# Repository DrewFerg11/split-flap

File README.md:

# split-flap
3D-printable split-flap modules, electronics, and firmware

[Documentation and demos](https://drewferg11.github.io/split-flap/) (site under development).

## Layout

| Folder | What | Release tag |
|---|---|---|
| [`pcb/`](pcb/) | KiCad boards; fab packages built locally and committed | `pcb/<board>/vX.Y` |
| [`hardware/`](hardware/) | 3D-printable and physical parts | `hw/<part>/vX.Y` |
| [`firmware/`](firmware/) | Shared module and controller firmware; built by CI | `fw/<target>/vX.Y.Z` |
| [`applications/`](applications/) | Displays built from the above (e.g. Premier League) | `app/<application>/vX.Y.Z` |

## License

Free to build, modify, and share for noncommercial use under
[CC BY-NC-SA 4.0](LICENSE.md), with a few extra permissions (paying a fab for your own
build, selling a used personal build, platform rewards on remixes). Commercial use needs
permission. See [LICENSE.md](LICENSE.md), [THIRD-PARTY-NOTICES.md](LICENSES/THIRD-PARTY-NOTICES.md),
and [CONTRIBUTING.md](.github/CONTRIBUTING.md).

This is original work; see the [Acknowledgements](LICENSE.md#acknowledgements) for the projects
we're grateful to.

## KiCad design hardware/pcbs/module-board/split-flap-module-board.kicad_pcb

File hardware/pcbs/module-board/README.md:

# Split-flap module board v0.1

**Status (2026-10-27): board #1 brought up** (power, SWD flash, LED, hall, encoder, motor drive all pass; see `design/DESIGN-1.md` section 14 and `firmware/ltm-bringup/`). **Next:** other 9 boards, ISEN, RS-485 + enumeration firmware.

**Status (2026-10-19): ordered.** ERC 0, DRC 0 errors / 0 unconnected; the files in `fab/` are what was ordered.

**Ordered 2026-10-19:** JLCPCB, 10 boards, Economic PCBA top side (green, 1.6 mm, HASL), est. ship 2026-10-23; C1 hand-solder caps from LCSC (20× C3151830, separate shipment).

Start with [`design/DESIGN-1.md`](design/DESIGN-1.md).

One small board per split-flap module (digit and name) of the league-table display
([`builds/league-table`](../../builds/league-table/README.md)): STM32G031 + DRV8870 driving one 12 V
N20 encoder motor, A3144 homing, RS-485 to a single ESP32 host, chained module-to-module through
right-angle headers on the board edges.

The hall sensor connector and pinout are the same as on the SplitFlap v5.1 board, so existing
sensor leads plug in.

```
design/
  DESIGN-1.md          requirements, decisions, parts, pin map, outline, open questions  <- read this
(project root)
  split-flap-module-board.kicad_pro/_sch    KiCad 10 project (generated by scripts/)
  split-flap-module-board-schematic.pdf
  split-flap-module-board.kicad_pcb         32 x 54 mm, 2 layers (generated by scripts/)
  split-flap-module-board.kicad_sym  project symbols (library sfmb:) (+12V_CHAIN/FUSED/LOCAL, GM3085E)
  fab/                 JLC package: gerbers/ + zip, BOM, CPL, STEP, layers PDF, check reports
    images/            top / bottom / 3D renders and screenshots
  scripts/             build.py: schematic + ERC + PDF + netlist
                       route_all.py: placement -> GND fan-out -> Freerouting -> stitch/fill -> silk ->
                       width audit -> DRC -> fab outputs (gen_board, stitch, autoroute, silk, widths,
                       outputs, jlc_cpl, snap, check_place)
```

```
python scripts/build.py        # schematic (seconds)
python scripts/route_all.py    # board + fab package (~10 min, Freerouting)
```

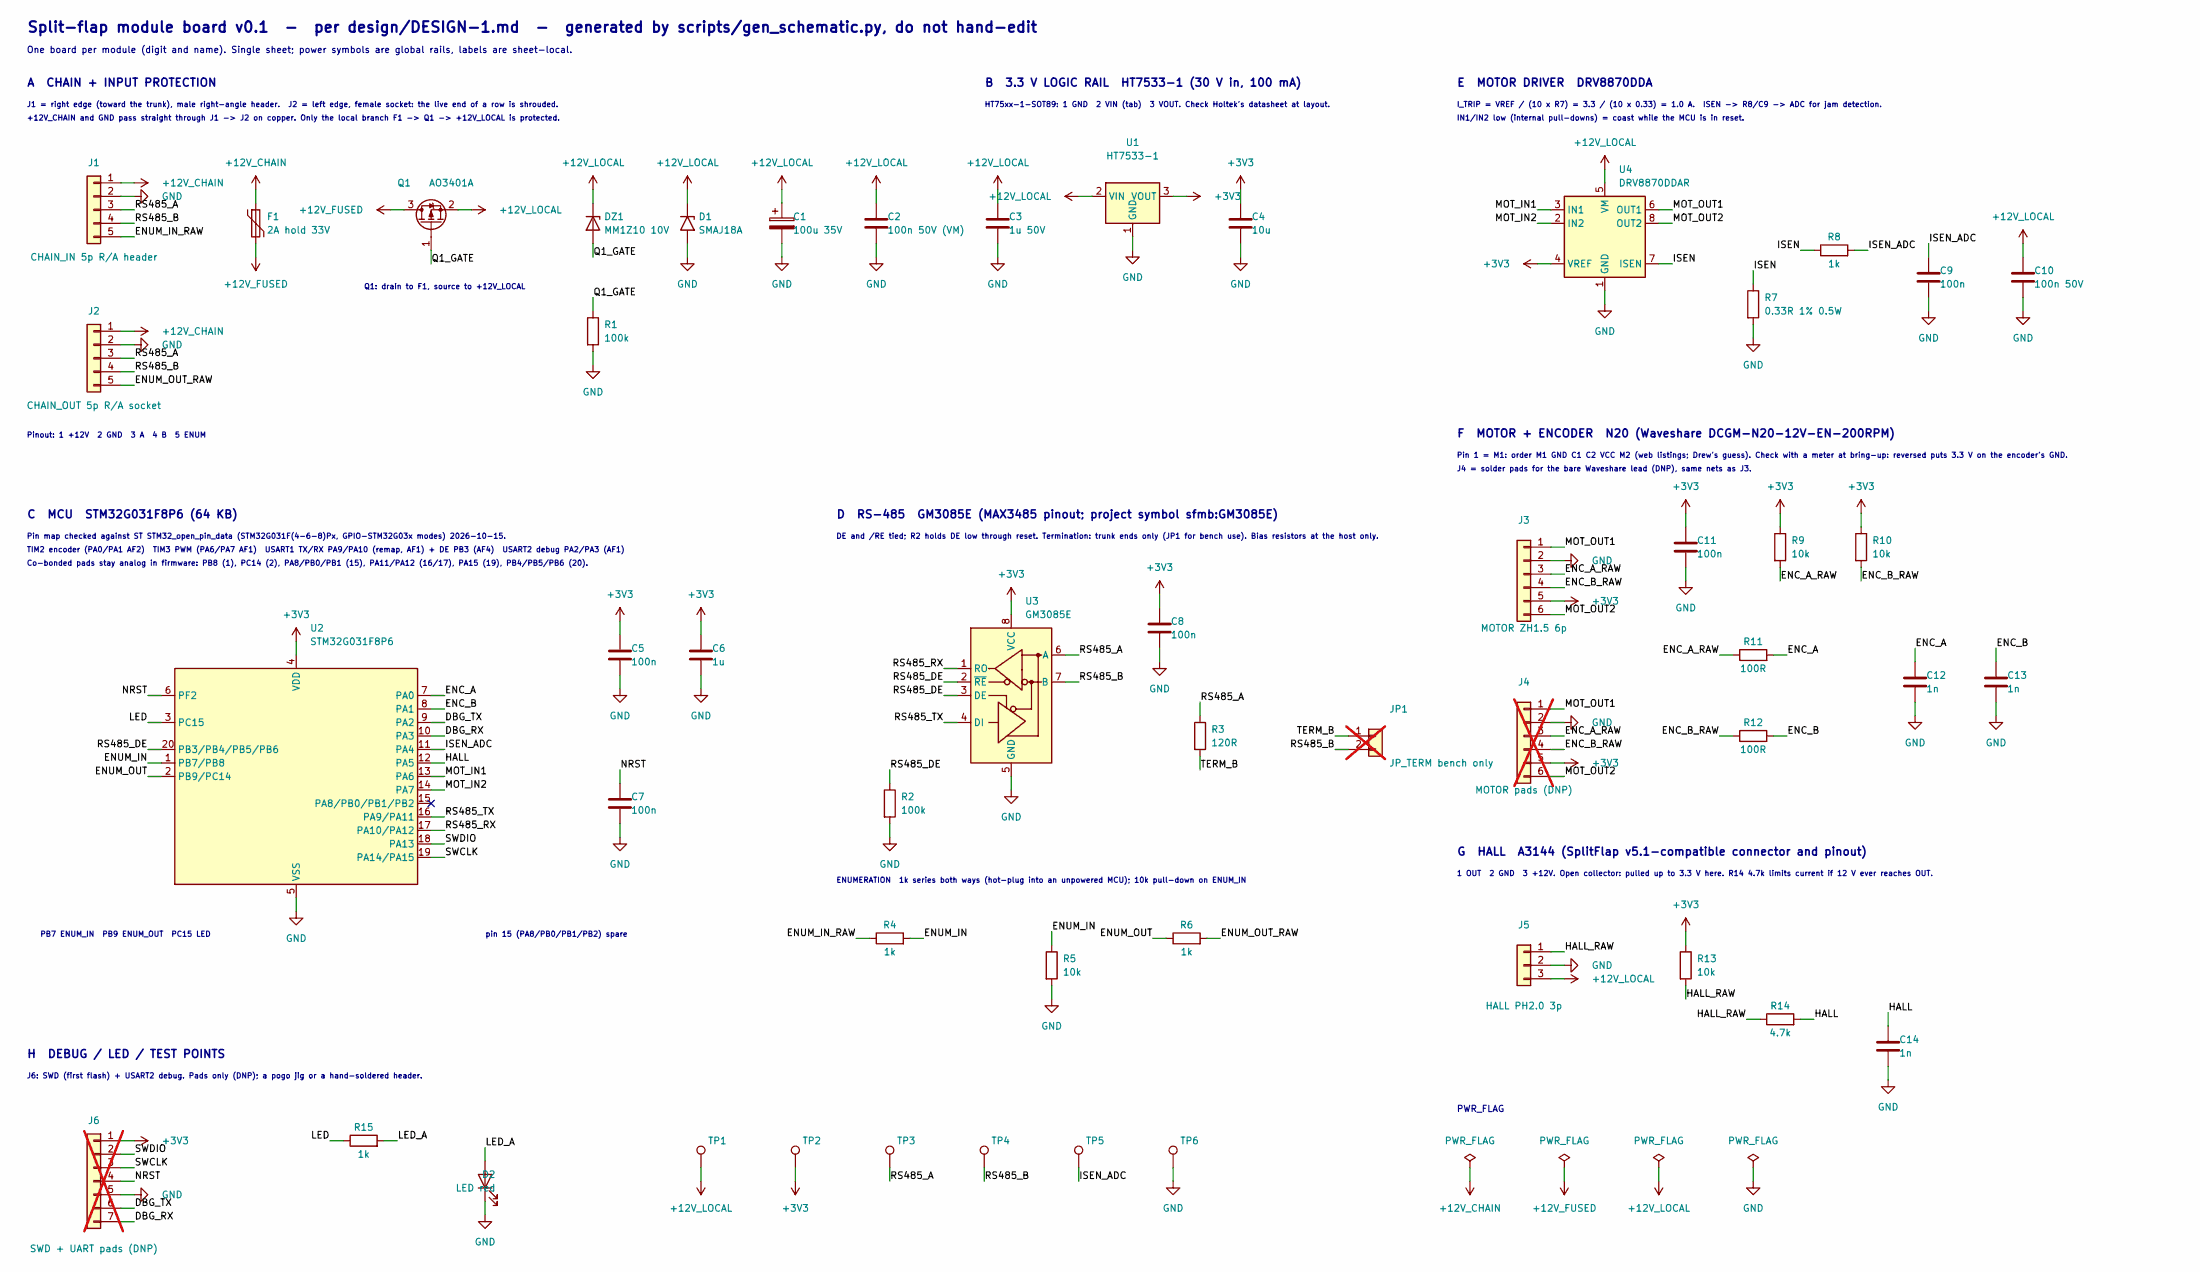
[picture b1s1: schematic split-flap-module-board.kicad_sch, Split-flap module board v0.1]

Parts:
C1: 100u 35V; CP_Elec_6.3x5.4; LCSC C3151830
C2: 100n 50V (VM); C_0603_1608Metric; LCSC C14663
C3: 1u 50V; C_0603_1608Metric; LCSC C15849
C4: 10u; C_0603_1608Metric; LCSC C19702
C5, C7, C8, C9, C11: 100n; C_0603_1608Metric; LCSC C14663
C6: 1u; C_0603_1608Metric; LCSC C15849
C10: 100n 50V; C_0603_1608Metric; LCSC C14663
C12, C13, C14: 1n; C_0603_1608Metric; LCSC C1588
D1: SMAJ18A; D_SMA; LCSC C908771
D2: LED red; LED_0603_1608Metric; LCSC C2286
DZ1: MM1Z10 10V; D_SOD-123; LCSC C107591
F1: 2A hold 33V; Fuse_1812_4532Metric; LCSC C7433877
J1: CHAIN_IN 5p R/A header; PinHeader_1x05_P2.54mm_Horizontal; LCSC C492413
J2: CHAIN_OUT 5p R/A socket; PinSocket_1x05_P2.54mm_Horizontal; LCSC C2897387
J3: MOTOR ZH1.5 6p; JST_ZH_B6B-ZR_1x06_P1.50mm_Vertical; LCSC C157984
J4: MOTOR pads (DNP); PinHeader_1x06_P2.54mm_Vertical; not fitted
J5: HALL PH2.0 3p; JST_PH_B3B-PH-K_1x03_P2.00mm_Vertical; LCSC C2320
J6: SWD + UART pads (DNP); PinHeader_1x07_P2.54mm_Vertical; not fitted
JP1: JP_TERM bench only; PinHeader_1x02_P2.54mm_Vertical; LCSC C492401; not fitted
Q1: AO3401A; SOT-23; LCSC C15127
R1, R2: 100k; R_0603_1608Metric; LCSC C25803
R3: 120R; R_0603_1608Metric; LCSC C22787
R4, R6, R8, R15: 1k; R_0603_1608Metric; LCSC C21190
R5, R9, R10, R13: 10k; R_0603_1608Metric; LCSC C25804
R7: 0.33R 1% 0.5W; R_1206_3216Metric; LCSC C858786
R11, R12: 100R; R_0603_1608Metric; LCSC C22775
R14: 4.7k; R_0603_1608Metric; LCSC C23162
TP1: +12V_LOCAL; TestPoint_Pad_D1.5mm
TP2: +3V3; TestPoint_Pad_D1.5mm
TP3: RS485_A; TestPoint_Pad_D1.5mm
TP4: RS485_B; TestPoint_Pad_D1.5mm
TP5: ISEN_ADC; TestPoint_Pad_D1.5mm
TP6: GND; TestPoint_Pad_D1.5mm
U1: HT7533-1; SOT-89-3; LCSC C14289
U2: STM32G031F8P6; TSSOP-20_4.4x6.5mm_P0.65mm; LCSC C529334
U3: GM3085E; SOIC-8_3.9x4.9mm_P1.27mm; LCSC C269864
U4: DRV8870DDAR; Texas_HTSOP-8-1EP_3.9x4.9mm_P1.27mm_EP2.95x4.9mm_Mask2.4x3.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; LCSC C86590

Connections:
+3V3: C4.1, C5.1, C6.1, C8.1, C11.1, J3.5, J4.5, J6.1, R9.1, R10.1, R13.1, TP2.1, U1.3 (VOUT), U2.4 (VDD), U3.8 (VCC), U4.4 (VREF)
+12V_CHAIN: F1.1, J1.1, J2.1
+12V_FUSED: F1.2, Q1.3 (D)
+12V_LOCAL: C1.1, C2.1, C3.1, C10.1, D1.1 (A1), DZ1.1 (K), J5.3, Q1.2 (S), TP1.1, U1.2 (VIN), U4.5 (VM)
/DBG_RX: J6.7, U2.10 (PA3)
/DBG_TX: J6.6, U2.9 (PA2)
/ENC_A: C12.1, R11.2, U2.7 (PA0)
/ENC_A_RAW: J3.3, J4.3, R9.2, R11.1
/ENC_B: C13.1, R12.2, U2.8 (PA1)
/ENC_B_RAW: J3.4, J4.4, R10.2, R12.1
/ENUM_IN: R4.2, R5.1, U2.1 (PB7/PB8)
/ENUM_IN_RAW: J1.5, R4.1
/ENUM_OUT: R6.1, U2.2 (PB9/PC14)
/ENUM_OUT_RAW: J2.5, R6.2
/HALL: C14.1, R14.2, U2.12 (PA5)
/HALL_RAW: J5.1, R13.2, R14.1
/ISEN: R7.1, R8.1, U4.7 (ISEN)
/ISEN_ADC: C9.1, R8.2, TP5.1, U2.11 (PA4)
/LED: R15.1, U2.3 (PC15)
/LED_A: D2.2 (A), R15.2
/MOT_IN1: U2.13 (PA6), U4.3 (IN1)
/MOT_IN2: U2.14 (PA7), U4.2 (IN2)
/MOT_OUT1: J3.1, J4.1, U4.6 (OUT1)
/MOT_OUT2: J3.6, J4.6, U4.8 (OUT2)
/NRST: C7.1, J6.4, U2.6 (PF2)
/Q1_GATE: DZ1.2 (A), Q1.1 (G), R1.1
/RS485_A: J1.3, J2.3, R3.1, TP3.1, U3.6 (A)
/RS485_B: J1.4, J2.4, JP1.2, TP4.1, U3.7 (B)
/RS485_DE: R2.1, U2.20 (PB3/PB4/PB5/PB6), U3.2 (~RE), U3.3 (DE)
/RS485_RX: U2.17 (PA10/PA12), U3.1 (RO)
/RS485_TX: U2.16 (PA9/PA11), U3.4 (DI)
/SWCLK: J6.3, U2.19 (PA14/PA15)
/SWDIO: J6.2, U2.18 (PA13)
/TERM_B: JP1.1, R3.2
GND: C1.2, C2.2, C3.2, C4.2, C5.2, C6.2, C7.2, C8.2, C9.2, C10.2, C11.2, C12.2, C13.2, C14.2, D1.2 (A2), D2.1 (K), J1.2, J2.2, J3.2, J4.2, J5.2, J6.5, R1.2, R2.2, R5.2, R7.2, TP6.1, U1.1 (GND), U2.5 (VSS), U3.5 (GND), U4.1 (GND), U4.9 (GND)

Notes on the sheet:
A CHAIN + INPUT PROTECTION
J1 = right edge (toward the trunk), male right-angle header. J2 = left edge, female socket: the live end of a row is shrouded.
+12V_CHAIN and GND pass straight through J1 -> J2 on copper. Only the local branch F1 -> Q1 -> +12V_LOCAL is protected.
Pinout: 1 +12V 2 GND 3 A 4 B 5 ENUM
Q1: drain to F1, source to +12V_LOCAL
B 3.3 V LOGIC RAIL HT7533-1 (30 V in, 100 mA)
HT75xx-1-SOT89: 1 GND 2 VIN (tab) 3 VOUT. Check Holtek's datasheet at layout.
C MCU STM32G031F8P6 (64 KB)
Pin map checked against ST STM32_open_pin_data (STM32G031F(4-6-8)Px, GPIO-STM32G03x modes) 2026-10-15.
TIM2 encoder (PA0/PA1 AF2) TIM3 PWM (PA6/PA7 AF1) USART1 TX/RX PA9/PA10 (remap, AF1) + DE PB3 (AF4) USART2 debug PA2/PA3 (AF1)
Co-bonded pads stay analog in firmware: PB8 (1), PC14 (2), PA8/PB0/PB1 (15), PA11/PA12 (16/17), PA15 (19), PB4/PB5/PB6 (20).
PB7 ENUM_IN PB9 ENUM_OUT PC15 LED
pin 15 (PA8/PB0/PB1/PB2) spare
D RS-485 GM3085E (MAX3485 pinout; project symbol sfmb:GM3085E)
DE and /RE tied; R2 holds DE low through reset. Termination: trunk ends only (JP1 for bench use). Bias resistors at the host only.
ENUMERATION 1k series both ways (hot-plug into an unpowered MCU); 10k pull-down on ENUM_IN
E MOTOR DRIVER DRV8870DDA
I_TRIP = VREF / (10 x R7) = 3.3 / (10 x 0.33) = 1.0 A. ISEN -> R8/C9 -> ADC for jam detection.
IN1/IN2 low (internal pull-downs) = coast while the MCU is in reset.
F MOTOR + ENCODER N20 (Waveshare DCGM-N20-12V-EN-200RPM)
Pin 1 = M1: order M1 GND C1 C2 VCC M2 (web listings; Drew's guess). Check with a meter at bring-up: reversed puts 3.3 V on the encoder's GND.
J4 = solder pads for the bare Waveshare lead (DNP), same nets as J3.
G HALL A3144 (SplitFlap v5.1-compatible connector and pinout)
1 OUT 2 GND 3 +12V. Open collector: pulled up to 3.3 V here. R14 4.7k limits current if 12 V ever reaches OUT.
H DEBUG / LED / TEST POINTS
J6: SWD (first flash) + USART2 debug. Pads only (DNP); a pogo jig or a hand-soldered header.
PWR_FLAG
Split-flap module board v0.1 - per design/DESIGN-1.md - generated by scripts/gen_schematic.py, do not hand-edit
One board per module (digit and name). Single sheet; power symbols are global rails, labels are sheet-local.

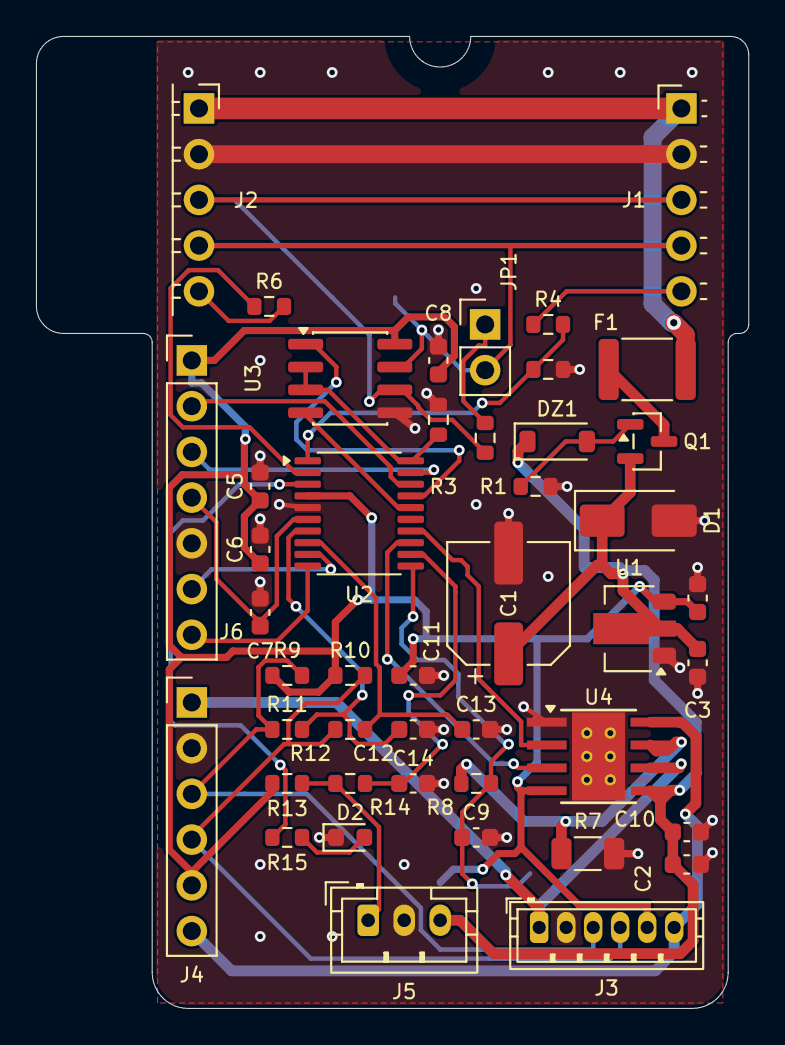
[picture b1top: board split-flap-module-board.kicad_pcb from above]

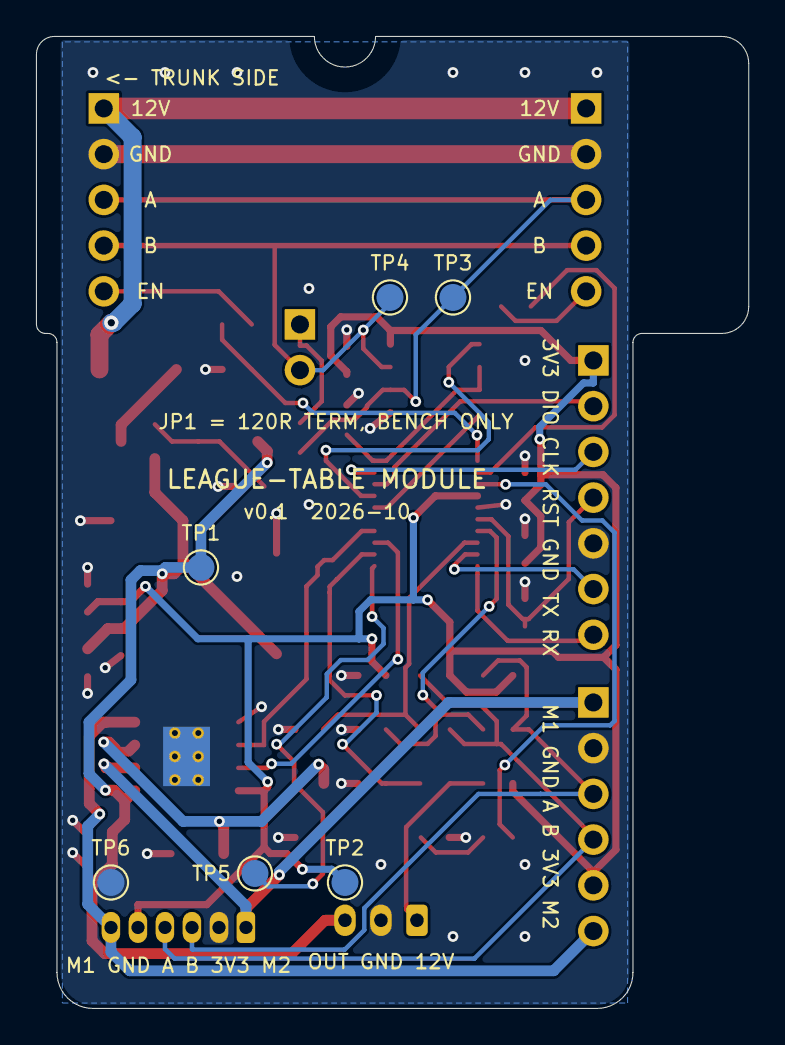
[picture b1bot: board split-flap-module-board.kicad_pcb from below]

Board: 2 copper layers, 39.6 x 54.0 mm, 51 parts (6 on the bottom side), 35 nets.

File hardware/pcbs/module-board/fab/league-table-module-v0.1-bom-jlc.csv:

Comment,Designator,Footprint,LCSC
1u,"C3,C6",C_0603_1608Metric,C15849
10u,C4,C_0603_1608Metric,C19702
100n,"C2,C5,C7,C8,C9,C10,C11",C_0603_1608Metric,C14663
1n,"C12,C13,C14",C_0603_1608Metric,C1588
SMAJ18A,D1,D_SMA,C908771
LED red,D2,LED_0603_1608Metric,C2286
MM1Z10 10V,DZ1,D_SOD-123,C107591
2A hold 33V,F1,Fuse_1812_4532Metric,C7433877
CHAIN_IN  5p R/A header,J1,PinHeader_1x05_P2.54mm_Horizontal,C492413
CHAIN_OUT  5p R/A socket,J2,PinSocket_1x05_P2.54mm_Horizontal,C2897387
MOTOR  ZH1.5 6p,J3,JST_ZH_B6B-ZR_1x06_P1.50mm_Vertical,C157984
HALL  PH2.0 3p,J5,JST_PH_B3B-PH-K_1x03_P2.00mm_Vertical,C2320
AO3401A,Q1,SOT-23,C15127
100k,"R1,R2",R_0603_1608Metric,C25803
120R,R3,R_0603_1608Metric,C22787
0.33R 1% 0.5W,R7,R_1206_3216Metric,C858786
10k,"R5,R9,R10,R13",R_0603_1608Metric,C25804
100R,"R11,R12",R_0603_1608Metric,C22775
4.7k,R14,R_0603_1608Metric,C23162
1k,"R4,R6,R8,R15",R_0603_1608Metric,C21190
HT7533-1,U1,SOT-89-3,C14289
STM32G031F8P6,U2,TSSOP-20_4.4x6.5mm_P0.65mm,C529334
GM3085E,U3,SOIC-8_3.9x4.9mm_P1.27mm,C269864
DRV8870DDAR,U4,Texas_HTSOP-8-1EP_3.9x4.9mm_P1.27mm_EP2.95x4.9mm_Mask2.4x3.1mm_ThermalVias,C86590

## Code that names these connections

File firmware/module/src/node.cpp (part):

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// Addressing: the default build is the same image on every board. It powers up unplaced (address 0) and the
// host places it over the bus, in ENUM chain order (sfbus.h).
//
//   PC15 LED                    PA0/PA1 ENC_A/B  TIM2 encoder mode (AF2)
//   PA6/PA7 MOT_IN1/IN2 TIM3    PA4 ISEN_ADC     PA5 HALL (low = magnet, EXTI)
//   PA9/PA10/PB3 USART1 bus     PB7 ENUM_IN      PB9 ENUM_OUT
//
// LED: unplaced = 2 Hz blink. Once placed, N blinks = this board's address, then a 1 Hz heartbeat. Lit while
// the motor runs and briefly on every frame addressed to it. C_IDENT blinks it fast for 3 s.
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  analogReadResolution(12);
  attachInterrupt(D_HALL, hallIsr, FALLING);

  __HAL_RCC_GPIOB_CLK_ENABLE();                // PB7 ENUM_IN: input with pull-down
  GPIOB->MODER &= ~(3u << 14);
  GPIOB->PUPDR = (GPIOB->PUPDR & ~(3u << 14)) | (2u << 14);
  enumOut(false);                              // PB9 ENUM_OUT: output, low until this module is placed
  GPIOB->MODER = (GPIOB->MODER & ~(3u << 18)) | (1u << 18);
  // Co-bonded pins (PB8, PC14, PA8, PB0-2, PA11/12, PA15, PB4-6) stay analog: design §7.1.

  bus_init(BAUD);
}
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
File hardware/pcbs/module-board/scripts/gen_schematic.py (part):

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# ============================================================================= C  MCU
T("C  MCU  STM32G031F8P6 (64 KB)", 20.32, 111.76)
T("Pin map checked against ST STM32_open_pin_data (STM32G031F(4-6-8)Px, GPIO-STM32G03x modes) 2026-10-15.", 20.32, 115.57, 1.0, False)
T("TIM2 encoder (PA0/PA1 AF2)  TIM3 PWM (PA6/PA7 AF1)  USART1 TX/RX PA9/PA10 (remap, AF1) + DE PB3 (AF4)  USART2 debug PA2/PA3 (AF1)", 20.32, 118.11, 1.0, False)
T("Co-bonded pads stay analog in firmware: PB8 (1), PC14 (2), PA8/PB0/PB1 (15), PA11/PA12 (16/17), PA15 (19), PB4/PB5/PB6 (20).", 20.32, 120.65, 1.0, False)
part("U2", "MCU_ST_STM32G0:STM32G031F8Px", 71.12, 160.02, {
    "4": "+3V3", "5": "GND", "6": "NRST",
    "1": "ENUM_IN", "2": "ENUM_OUT", "3": "LED", "20": "RS485_DE",
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    "18": "SWDIO", "19": "SWCLK"},
    value="STM32G031F8P6", fp="Package_SO:TSSOP-20_4.4x6.5mm_P0.65mm", lcsc="C529334",
    ref_at=(73.66, 132.08), val_at=(73.66, 134.62), justify="left")
T("PB7 ENUM_IN  PB9 ENUM_OUT  PC15 LED", 22.86, 190.5, 1.0, False)
T("pin 15 (PA8/PB0/PB1/PB2) spare", 106.68, 190.5, 1.0, False)
C("C5", 132.08, 137.16, "+3V3", "GND", "100n", LCSC["c100n"])
C("C6", 147.32, 137.16, "+3V3", "GND", "1u", LCSC["c1u"])
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C("C13", 391.16, 142.24, "ENC_B", "GND", "1n", LCSC["c1n"])

# ============================================================================= G  hall
T("G  HALL  A3144 (SplitFlap v5.1-compatible connector and pinout)", 289.56, 175.26)
T("1 OUT  2 GND  3 +12V. Open collector: pulled up to 3.3 V here. R14 4.7k limits current if 12 V ever reaches OUT.", 289.56, 179.07, 1.0, False)
part("J5", "Connector_Generic:Conn_01x03", 302.26, 195.58, {"1": "HALL_RAW", "2": "GND", "3": "+12V_LOCAL"}, mirror=True,
     value="HALL  PH2.0 3p", fp="Connector_JST:JST_PH_B3B-PH-K_1x03_P2.00mm_Vertical", lcsc="C2320",
     ref_at=(302.26, 187.96), val_at=(302.26, 203.2))
R("R13", 332.74, 195.58, "+3V3", "HALL_RAW", "10k", LCSC["r10k"])
R("R14", 350.52, 205.74, "HALL_RAW", "HALL", "4.7k", LCSC["r4k7"], horizontal=True)
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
